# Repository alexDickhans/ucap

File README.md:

# uCap v1

uCap v1 is a USB-powered board for capacitive sensing. An STM32G474 reads a sense pad on one mounting hole, and four JST SH sockets carry I2C. The name is the one printed on the back of the board. Open the project in KiCad 10 (`ucap/ucap.kicad_pro`).

The board is 24.9 mm by 24.4 mm.

## Pictures

Top of the board, USB edge up. The four white housings are the JST SH sockets. J1, along the top edge, is the USB-C footprint: the yellow slots are its plated shell holes, and the connector body is not drawn. U1 is the QFN footprint: the yellow grid is the exposed pad, and the chip body is not drawn. The silk dot at the lower-left corner of that land is pin 1.

Bottom of the board, USB edge still up. J2 is the SWD socket. U3 is the regulator and L1 is the inductor. TP3 and TP4 are the round pads marked GND and 3v3. The white block and the yellow slots along the top of this view are the underside of the connectors on the top.

The buck, from the 5 V input through U3. EN is tied to VIN. The wire leaving to the right is the switch node and continues in the next figure.

The rest of the 3.3 V rail. L1 is 2.2 µH. C9, 1 µF, sits on +3V3A after the ferrite.

USB-C power and data. Both CC pins have 5.1 kΩ to ground. U2 is the USBLC6-2SC6 on D+ and D−.

The four I2C sockets on the schematic. J3 is I2C 0 and J4 is I2C 1. This sheet draws J6 at the lower left and J5 at the lower right. On the board, I2C 2 (J5) is the lower left socket and I2C 3 (J6) is the lower right. The capacitors drawn here are 4.7 µF and 100 nF.

The sense circuit. H1 is the sense node. H2 is ground. D2 is the bidirectional TVS, SD05C-01FTG.

The microcontroller, the status LED, and the SWD socket. PG10 is reset. PB8 is BOOT0.

## Connectors, holes, and test points

Silkscreen reference designators match the table. Pin 1 of the JST sockets is not numbered on the silk. The ends below were taken from the pad coordinates on this board.

Looking at the top, with the USB edge up:

| Silk | Side | What you see | Pins |
| --- | --- | --- | --- |
| J1 | top | USB-C footprint at the top edge. The plug enters from that edge. | VBUS (A4, A9, B4, B9) is +5 V. CC1 and CC2 each have 5.1 kΩ to ground. D+ is tied between A6 and B6, and D− between A7 and B7, so either plug orientation works. Shield is ground. SuperSpeed and SBU pins are open. |
| J3, under “I2C 0” | top | Upper-left JST SH, 4 pin. Contacts are on the left side of the housing. | From the USB edge: 1 ground, 2 +3.3 V, 3 SDA (PB9), 4 SCL (PA15). Pin 1 is the contact nearest the USB edge. |
| J4, under “I2C 1” | top | Upper-right JST SH, 4 pin. Contacts are on the right side of the housing. | From the USB edge: 4 SCL (PC4), 3 SDA (PF0), 2 +3.3 V, 1 ground. Pin 1 is the contact away from the USB edge. |
| J5, under “I2C 2” | top | Lower-left JST SH, 4 pin. Same orientation as J3. | From the top of that socket: 1 ground, 2 +3.3 V, 3 SDA (PC11), 4 SCL (PA8). |
| J6, under “I2C 3” | top | Lower-right JST SH, 4 pin. Same orientation as J4. | From the top of that socket: 4 SCL (PC6), 3 SDA (PB7), 2 +3.3 V, 1 ground. Pin 1 is the lower contact. |
| 1 | top | The right-hand 2.2 mm hole, H1. | The sense node, the same net as D2 and R5. |
| GND | top | The left-hand 2.2 mm hole, H2. The GND silk sits between the holes. | Ground. |
| J2 | bottom | 3-pin JST SH. In the bottom picture, its contacts point away from the USB edge. | Left contact is pin 1, SWCLK (PA14). Middle is ground. Right contact is pin 3, SWDIO (PA13). No 3.3 V and no reset on this socket. |
| GND by TP3 | bottom | Round pad | Ground. |
| 3v3 by TP4 | bottom | Round pad | +3.3 V, the regulator output. |

Each I2C socket has a 4.7 µF capacitor and a 100 nF capacitor from its 3.3 V pin to ground.

## Power

Plug in USB. That is the only power input. VBUS is +5 V, and either orientation of the plug works. The 5.1 kΩ resistors on CC1 and CC2 make this a USB device. The host has to supply 5 V.

There is no battery connector, no charger, and no diode between VBUS and the regulator. U3, a TPS563208, runs whenever VBUS is present because its enable pin is tied to its input. L1 is 2.2 µH. R3, 33.2 kΩ, and R4, 10 kΩ, set the feedback. The TPS563208 reference is 0.768 V, so the output is about 3.32 V. FB1, 600 Ω at 100 MHz, feeds +3V3A, which is VDDA and VREF+.

Pin 2 of J3, J4, J5, and J6 is that 3.3 V output. Do not power the board from those pins.

U1 pin 1, VBAT, is not connected. PG10 (pin 7) is reset: R11, 10 kΩ, pulls it up to 3.3 V, and C24, 100 nF, goes to ground. There is no reset button, and J2 does not carry reset, so a debugger on J2 cannot reset the chip. PB8 (pin 46) is BOOT0. R10, 10 kΩ, holds it at ground. If that pin is high at reset, the chip can boot the system loader instead of flash.

D1 is the status LED. Its comment in the BOM is STAT. The part is a green 0805 LED. The cathode, pad 1, is the end toward the I2C sockets. The anode goes to PA5. A high on PA5 lights it. R9, 470 Ω, is between the cathode and ground.

The two holes are part of the circuit. H1, the hole by the silk “1”, is the sense electrode. PA0 drives it through R5, 1 MΩ. PA1 reads it through R6, 220 Ω. D2 clamps that node to ground. H2 is ground. R7 and R8, both 10 kΩ, divide 3.3 V in half for the comparator threshold on PA4.

## Manufacture

Order a 6-layer board, 1.6 mm thick, 1 oz (35 µm) copper on all six layers. The stackup in the board file is FR4 with 0.1 mm prepreg, 0.535 mm core, 0.1 mm prepreg, 0.535 mm core, and 0.1 mm prepreg. A prototype shop can use its standard 6-layer 1.6 mm stack. Impedance control is not required. The board file leaves the surface finish unset, so a normal prototype finish is fine.

The smallest trace is 0.15 mm. The smallest space is 0.127 mm. The smallest via is a 0.45 mm pad with a 0.20 mm drill. There are also 0.6 mm vias with a 0.30 mm drill. Every hole is plated, including the four USB shell slots and the two 2.2 mm holes. There is no unplated drill file.

The inner ground fills and the inner 3.3 V fill come to 0.30 mm of the outline. A shop whose copper-to-edge limit is 0.2 mm will pass. A shop whose limit is 0.3 mm may flag those fills. Leave the connector where it is. Accept that warning when the USB pads and the holes are still intact in the preview. The USB silkscreen also runs into the outline. That is expected.

Gerbers, the drill, the BOM, and the placement file were exported from this revision.

`ucap/production/ucap.zip` contains the six copper layers, both solder masks, both silkscreens, both pastes, the board outline, and one Excellon drill. Extensions are Protel. Coordinates are millimeters, absolute origin, and the same origin as the placement file, including the negative Y. Soldermask is subtracted from the silkscreen. The zip has no drill map, no job file, and no empty unplated-hole file.

`ucap/production/ucap-bom.csv` columns are Designator, Comment, Footprint, Qty, and LCSC Part #. Comment is the value on the symbol. H1 and H2 are left off on purpose: they are marked do-not-populate and excluded from the BOM. The holes are still drilled.

A few comments do not say what the assembler expects:

- D1’s comment is STAT. Order the green 0805 LED, Hubei KENTO KT-0805G, LCSC C2297.
- J1’s comment is USB_C_Receptacle_USB2.0_14P. The footprint and LCSC C134092 are the Molex 105450-0101, a 24-position Type-C receptacle. Only USB 2.0 is wired.
- FB1 is a ferrite bead, Sunlord GZ1608D601TF, 600 Ω at 100 MHz, on an 0603 inductor land. It is not a wound inductor.
- L1’s footprint is named L_APV_ANR4020. The part is a 4×4 mm 2.2 µH inductor, Sunlord WPN4020H2R2MT, LCSC C98361.
- U3’s footprint is named SOT-23-6. The part is the TPS563208DDCR in TSOT-23-6, which uses that land.
- TP3 and TP4 are copper pads. The LCSC cell is blank because there is nothing to buy. U1 is the STM32G474CEU6, LCSC C1235412. D2 is the Littelfuse SD05C-01FTG, LCSC C118264.

`ucap/production/ucap-pos.csv` is one KiCad placement file for both sides, in millimeters. DNP parts are excluded, so H1 and H2 are not in it. The header is Designator, Val, Package, Mid X, Mid Y, Rotation, Layer. Y is negative, matching the gerbers. Bottom X is not negated. Bottom rotations are KiCad’s. Many assemblers mirror the bottom. Check the placement preview before paying.

Parts that are easy to rotate wrong: U1, U2, U3, D1, J1, J2, and every part on the bottom. Those bottom parts are C3, C4, C6, C7, C9, C15, C24, D2, FB1, J2, L1, R3, R4, R5, R6, R7, R8, R10, R11, TP3, TP4, and U3. On the top, U1 pin 1 is the lower-left corner of the land. D1’s cathode is the end toward the I2C sockets. J1’s opening faces the top edge. On the bottom picture, U3 pin 1 (ground) is the lower pin on the right side of the package, and J2 pin 1 is the left contact. D2 is bidirectional, so turning it around does not swap the circuit.

## Firmware

PlatformIO firmware for the STM32G474 lives in [`firmware/`](firmware/README.md). It drives the COMP1+TIM2 capacitance path, the four Qwiic I2C buses, an LIS3MDL magnetometer, and up to three SparkFun VL53L5CX ToF imagers.

## ROS 2

[`ros2/ucap_sensor/`](ros2/ucap_sensor/README.md) is an `ament_python` node that reads the board’s USB CDC telemetry (115200) and publishes capacitance, ADC, magnetometer, and ToF topics.

## Design files

- `ucap/ucap.kicad_pro`, `ucap/ucap.kicad_sch`, `ucap/ucap.kicad_pcb` — KiCad 10 project
- `ucap/production/ucap.zip` — gerbers and drill
- `ucap/production/ucap-bom.csv` — bill of materials
- `ucap/production/ucap-pos.csv` — placement, both sides
- `firmware/` — board bring-up and sensor firmware
- `ros2/ucap_sensor/` — ROS 2 USB CDC host node

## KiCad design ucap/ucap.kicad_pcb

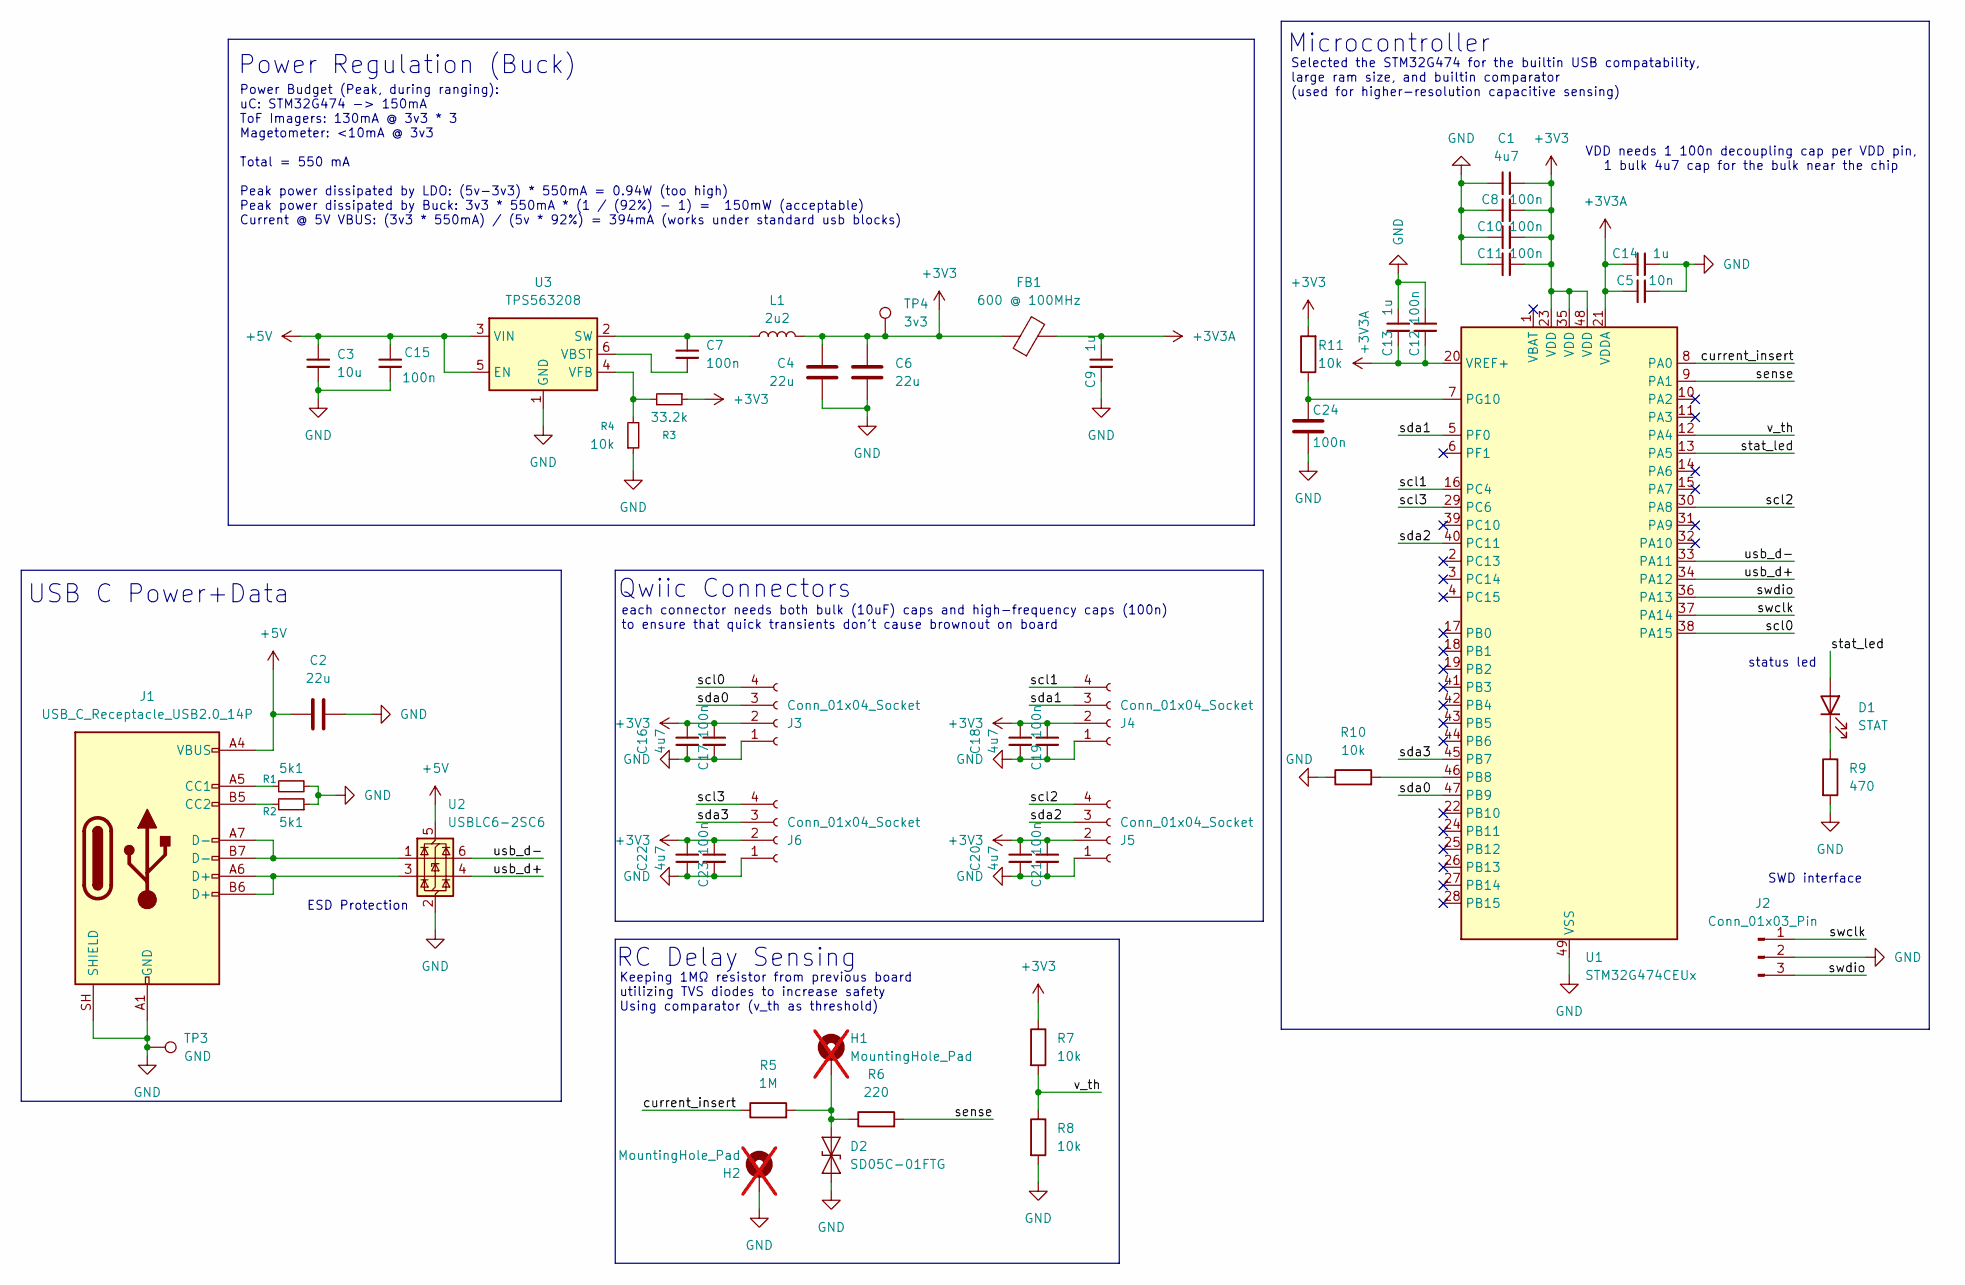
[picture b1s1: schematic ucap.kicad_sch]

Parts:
C1, C16, C18, C20, C22: 4u7; C_0603_1608Metric; LCSC Part # C19666
C2: 22u; C_1206_3216Metric; LCSC Part # C12891
C3: 10u; C_0805_2012Metric; LCSC Part # C15850
C4, C6: 22u; C_0805_2012Metric; LCSC Part # C45783
C5: 10n; C_0402_1005Metric; LCSC Part # C1524
C7, C8, C10, C11, C12, C15, C17, C19, C21, C23, C24: 100n; C_0402_1005Metric; LCSC Part # C1525
C9, C13, C14: 1u; C_0402_1005Metric; LCSC Part # C52923
D1: STAT; LED_0805_2012Metric; LCSC Part # C2297
D2: SD05C-01FTG; D_SOD-323; LCSC Part # C118264
FB1: 600 @ 100MHz; L_0603_1608Metric; LCSC Part # C1002
H1, H2: MountingHole_Pad; MountingHole_2.2mm_M2_DIN965_Pad; not fitted
J1: USB_C_Receptacle_USB2.0_14P; USB_C_Receptacle_Molex_105450-0101; LCSC Part # C134092
J2: Conn_01x03_Pin; JST_SH_BM03B-SRSS-TB_1x03-1MP_P1.00mm_Vertical; LCSC Part # C160389
J3, J4, J5, J6: Conn_01x04_Socket; JST_SH_BM04B-SRSS-TB_1x04-1MP_P1.00mm_Vertical; LCSC Part # C160390
L1: 2u2; L_APV_ANR4020; LCSC Part # C98361
R1, R2: 5k1; R_0402_1005Metric; LCSC Part # C25905
R3: 33.2k; R_0402_1005Metric; LCSC Part # C122548
R4, R7, R8, R10, R11: 10k; R_0402_1005Metric; LCSC Part # C25744
R5: 1M; R_0402_1005Metric; LCSC Part # C26083
R6: 220; R_0402_1005Metric; LCSC Part # C25091
R9: 470; R_0402_1005Metric; LCSC Part # C25117
TP3: GND; TestPoint_Pad_D2.0mm
TP4: 3v3; TestPoint_Pad_D2.0mm
U1: STM32G474CEUx; QFN-48-1EP_7x7mm_P0.5mm_EP5.6x5.6mm; LCSC Part # C1235412
U2: USBLC6-2SC6; SOT-23-6; LCSC Part # C7519
U3: TPS563208; SOT-23-6; LCSC Part # C468250

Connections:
+3V3: C1.2, C4.2, C6.2, C8.2, C10.2, C11.2, C16.2, C17.2, C18.2, C19.2, C20.2, C21.2, C22.2, C23.2, FB1.1, J3.2, J4.2, J5.2, J6.2, L1.2, R3.1, R7.1, R11.2, TP4.1 (1_1), U1.23 (VDD), U1.35 (VDD), U1.48 (VDD)
+3V3A: C5.1, C9.2, C12.1, C13.1, C14.1, FB1.2, U1.20 (VREF+), U1.21 (VDDA)
+5V: C2.2, C3.1, C15.2, J1.A4 (VBUS), J1.A9 (VBUS), J1.B4 (VBUS), J1.B9 (VBUS), U2.5 (VBUS), U3.3 (VIN), U3.5 (EN)
/current_insert: R5.1, U1.8 (PA0)
/scl0: J3.4, U1.38 (PA15)
/scl1: J4.4, U1.16 (PC4)
/scl2: J5.4, U1.30 (PA8)
/scl3: J6.4, U1.29 (PC6)
/sda0: J3.3, U1.47 (PB9)
/sda1: J4.3, U1.5 (PF0)
/sda2: J5.3, U1.40 (PC11)
/sda3: J6.3, U1.45 (PB7)
/sense: R6.2, U1.9 (PA1)
/stat_led: D1.2 (A), U1.13 (PA5)
/swclk: J2.1, U1.37 (PA14)
/swdio: J2.3, U1.36 (PA13)
/usb_d+: U1.34 (PA12), U2.4 (I/O2)
/usb_d-: U1.33 (PA11), U2.6 (I/O1)
/v_th: R7.2, R8.1, U1.12 (PA4)
GND: C1.1, C2.1, C3.2, C4.1, C5.2, C6.1, C8.1, C9.1, C10.1, C11.1, C12.2, C13.2, C14.2, C15.1, C16.1, C17.1, C18.1, C19.1, C20.1, C21.1, C22.1, C23.1, C24.2, D2.2 (A2), H2.1 (1_1), J1.A1 (GND), J1.A12 (GND), J1.B1 (GND), J1.B12 (GND), J1.SH (SHIELD), J2.2, J3.1, J4.1, J5.1, J6.1, R1.2, R2.1, R4.1, R8.2, R9.2, R10.1, TP3.1 (1_1), U1.49 (VSS), U2.2 (GND), U3.1 (GND)
unnamed: D1.1 (K), R9.1
unnamed: D2.1 (A1), H1.1 (1_1), R5.2, R6.1
unnamed: J1.A5 (CC1), R1.1
unnamed: J1.B5 (CC2), R2.2
unnamed: J1.A6 (D+), J1.B6 (D+), U2.3 (I/O2)
unnamed: J1.A7 (D-), J1.B7 (D-), U2.1 (I/O1)
unnamed: R10.2, U1.46 (PB8)
unnamed: C24.1, R11.1, U1.7 (PG10)
unnamed: C7.1, L1.1, U3.2 (SW)
unnamed: C7.2, U3.6 (VBST)
unnamed: R3.2, R4.2, U3.4 (VFB)

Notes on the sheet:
status led
each connector needs both bulk (10uF) caps and high-frequency caps (100n) to ensure that quick transients don't cause brownout on board
Power Budget (Peak, during ranging): uC: STM32G474 -> 150mA ToF Imagers: 130mA @ 3v3 * 3 Magetometer: <10mA @ 3v3 Total = 550 mA Peak power dissipated by LDO: (5v-3v3) * 550mA = 0.94W (too high) Peak power dissipated by Buck: 3v3 * 550mA * (1 / (92%) - 1) = 150mW (acceptable) Current @ 5V VBUS: (3v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
Microcontroller
SWD interface
ESD Protection
Power Regulation (Buck)
Qwiic Connectors
RC Delay Sensing
Selected the STM32G474 for the builtin USB compatability, large ram size, and builtin comparator (used for higher-resolution capacitive sensing)
USB C Power+Data
Keeping 1MΩ resistor from previous board utilizing TVS diodes to increase safety Using comparator (v_th as threshold)
VDD needs 1 100n decoupling cap per VDD pin, 1 bulk 4u7 cap for the bulk near the chip

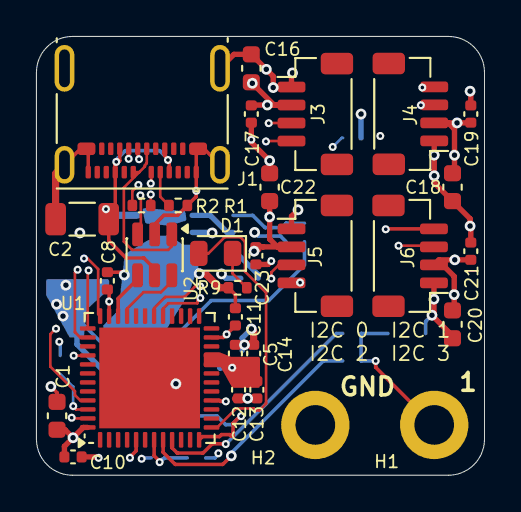
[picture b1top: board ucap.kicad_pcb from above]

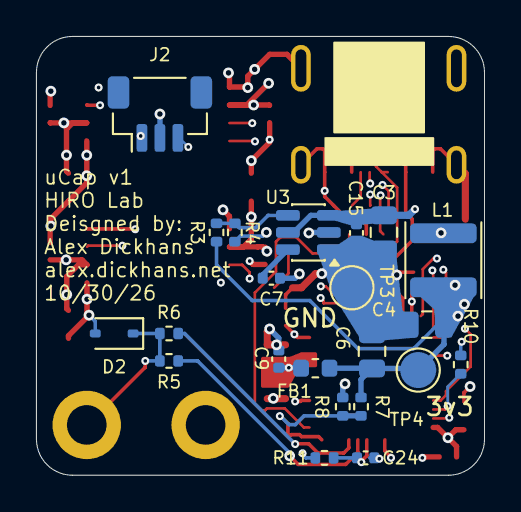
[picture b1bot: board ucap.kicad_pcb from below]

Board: 6 copper layers, 24.9 x 24.4 mm, 52 parts (22 on the bottom side), 31 nets.

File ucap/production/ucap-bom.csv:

"Designator","Comment","Footprint","Qty","LCSC Part #"
"C1,C16,C18,C20,C22","4u7","Capacitor_SMD:C_0603_1608Metric","5","C19666"
"C2","22u","Capacitor_SMD:C_1206_3216Metric","1","C12891"
"C3","10u","Capacitor_SMD:C_0805_2012Metric","1","C15850"
"C4,C6","22u","Capacitor_SMD:C_0805_2012Metric","2","C45783"
"C5","10n","Capacitor_SMD:C_0402_1005Metric","1","C1524"
"C7,C8,C10,C11,C12,C15,C17,C19,C21,C23,C24","100n","Capacitor_SMD:C_0402_1005Metric","11","C1525"
"C9,C13,C14","1u","Capacitor_SMD:C_0402_1005Metric","3","C52923"
"D1","STAT","LED_SMD:LED_0805_2012Metric","1","C2297"
"D2","SD05C-01FTG","Diode_SMD:D_SOD-323","1","C118264"
"FB1","600 @ 100MHz","Inductor_SMD:L_0603_1608Metric","1","C1002"
"J1","USB_C_Receptacle_USB2.0_14P","Connector_USB:USB_C_Receptacle_Molex_105450-0101","1","C134092"
"J2","Conn_01x03_Pin","Connector_JST:JST_SH_BM03B-SRSS-TB_1x03-1MP_P1.00mm_Vertical","1","C160389"
"J3,J4,J5,J6","Conn_01x04_Socket","Connector_JST:JST_SH_BM04B-SRSS-TB_1x04-1MP_P1.00mm_Vertical","4","C160390"
"L1","2u2","Inductor_SMD:L_APV_ANR4020","1","C98361"
"R1,R2","5k1","Resistor_SMD:R_0402_1005Metric","2","C25905"
"R3","33.2k","Resistor_SMD:R_0402_1005Metric","1","C122548"
"R4,R7,R8,R10,R11","10k","Resistor_SMD:R_0402_1005Metric","5","C25744"
"R5","1M","Resistor_SMD:R_0402_1005Metric","1","C26083"
"R6","220","Resistor_SMD:R_0402_1005Metric","1","C25091"
"R9","470","Resistor_SMD:R_0402_1005Metric","1","C25117"
"TP3","GND","TestPoint:TestPoint_Pad_D2.0mm","1",""
"TP4","3v3","TestPoint:TestPoint_Pad_D2.0mm","1",""
"U1","STM32G474CEUx","Package_DFN_QFN:QFN-48-1EP_7x7mm_P0.5mm_EP5.6x5.6mm","1","C1235412"
"U2","USBLC6-2SC6","Package_TO_SOT_SMD:SOT-23-6","1","C7519"
"U3","TPS563208","Package_TO_SOT_SMD:SOT-23-6","1","C468250"

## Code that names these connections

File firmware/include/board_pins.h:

#pragma once

/*
 * uCap v1 pin map — sourced from schematic labels + README connector table.
 * Do not invent alternate nets; every #define below is on the PCB.
 *
 * MCU: STM32G474CEUx (U1)
 */

#include <Arduino.h>

/* ---- Capacitance sense (RC Delay Sensing sheet) ----
 * PA0  current_insert  — GPIO charge drive through R5 (1 MΩ) to H1
 * PA1  sense           — COMP1_INP (also ADC1_IN2 / ADC2_IN2)
 * PA4  v_th            — COMP1_INM from R7/R8 divider (also ADC2_IN17)
 */
static constexpr uint32_t PIN_CURRENT_INSERT = PA0;
static constexpr uint32_t PIN_SENSE          = PA1;
static constexpr uint32_t PIN_V_TH           = PA4;

/* Charge resistor on the board (R5). */
static constexpr float CAP_R_OHMS = 1'000'000.0f;

/* ---- Status LED (D1 STAT) ----
 * PA5 high → LED on (anode to PA5, R9 470 Ω to cathode/GND).
 */
static constexpr uint32_t PIN_STAT_LED = PA5;

/* ---- USB FS (J1) ---- */
static constexpr uint32_t PIN_USB_DM = PA11;
static constexpr uint32_t PIN_USB_DP = PA12;

/* ---- SWD (J2) ---- */
static constexpr uint32_t PIN_SWDIO = PA13;
static constexpr uint32_t PIN_SWCLK = PA14;

/* ---- Four independent Qwiic I2C buses (J3–J6) ----
 * Each maps to a distinct STM32 I2C peripheral (AF from KiCad symbol).
 *
 * Bus  Silk  Conn  SDA   SCL    Peripheral
 * 0    I2C 0 J3    PB9   PA15   I2C1
 * 1    I2C 1 J4    PF0   PC4    I2C2
 * 2    I2C 2 J5    PC11  PA8    I2C3
 * 3    I2C 3 J6    PB7   PC6    I2C4
 */
static constexpr uint32_t PIN_I2C0_SDA = PB9;
static constexpr uint32_t PIN_I2C0_SCL = PA15;
static constexpr uint32_t PIN_I2C1_SDA = PF0;
static constexpr uint32_t PIN_I2C1_SCL = PC4;
static constexpr uint32_t PIN_I2C2_SDA = PC11;
static constexpr uint32_t PIN_I2C2_SCL = PA8;
static constexpr uint32_t PIN_I2C3_SDA = PB7;
static constexpr uint32_t PIN_I2C3_SCL = PC6;

static constexpr unsigned UCAP_I2C_BUS_COUNT = 4;
static constexpr unsigned UCAP_TOF_MAX       = 3;

/*
 * Default sensor socket assignment (PCB does not silk-label sensors;
 * sockets are identical Qwiic. This mapping is firmware policy):
 *   I2C0 (J3) — Adafruit #4022 LIS3MDL magnetometer
 *   I2C1 (J4) — VL53L5CX ToF #0
 *   I2C2 (J5) — VL53L5CX ToF #1
 *   I2C3 (J6) — VL53L5CX ToF #2
 */
static constexpr unsigned BUS_MAG   = 0;
static constexpr unsigned BUS_TOF0  = 1;
static constexpr unsigned BUS_TOF1  = 2;
static constexpr unsigned BUS_TOF2  = 3;
